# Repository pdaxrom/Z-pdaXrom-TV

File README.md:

# Z-pdaXrom-TV
FPGA board with TV out

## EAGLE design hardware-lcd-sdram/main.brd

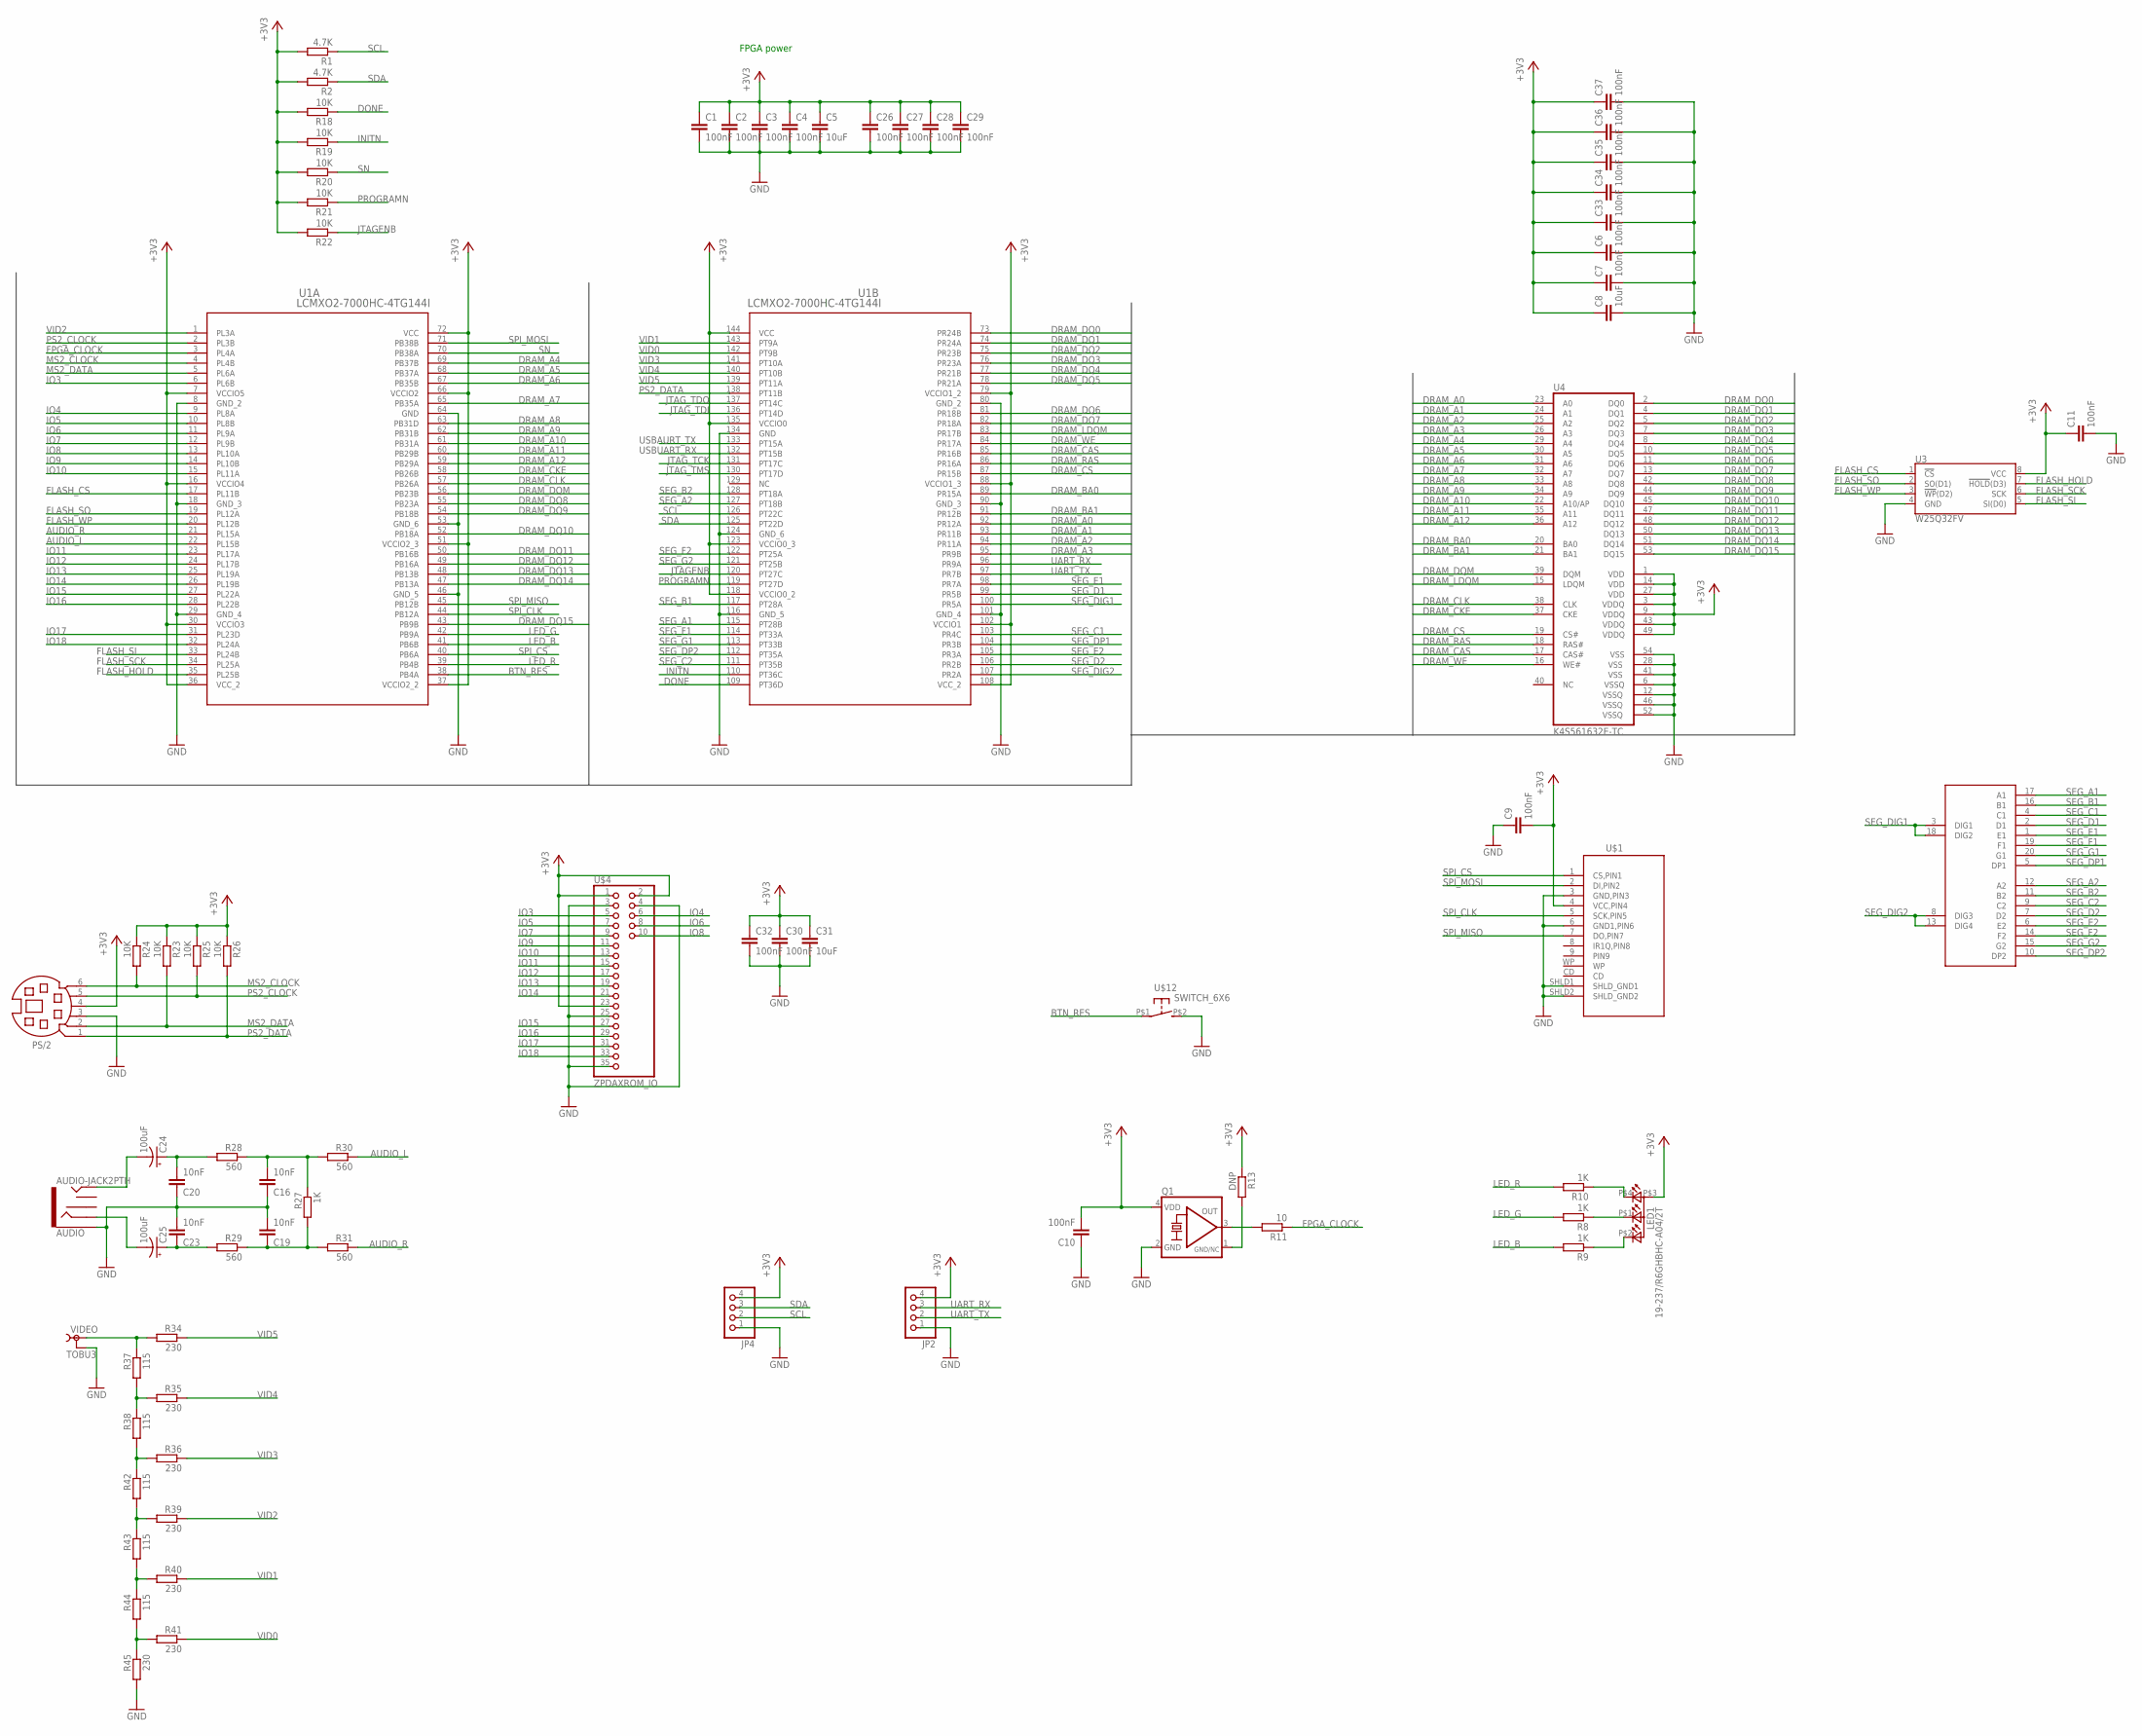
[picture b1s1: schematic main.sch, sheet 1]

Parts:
AUDIO: AUDIO-JACK2PTH; AUDIO-JACK
C1, C2, C3, C4, C6, C7, C9, C10, C11, C26, C27, C28, C29, C30, C32, C33, C34, C35, C36, C37: 100nF; C0603
C5, C8, C31: 10uF; C0805
C16, C19, C20, C23: 10nF; C0603
C24, C25: 100uF; EIA7343
JP2, JP4: PINHD-1X4; 1X04
LED1: 19-237/R6GHBHC-A04/2T
PS/2: MD06SS; MDIN06SS
Q1: KXO-TCXO-CMOS-82; 7.0X5.0_KXO-82-TCXO
R1, R2: 4.7K; R0603
R8, R9, R10, R27: 1K; R0603
R11: 10; R0603
R13: DNP; R0603
R18, R19, R20, R21, R22, R23, R24, R25, R26: 10K; R0603
R28, R29, R30, R31: 560; R0603
R34, R35, R36, R39, R40, R41, R45: 230; R0603
R37, R38, R42, R43, R44: 115; R0603
U1: LCMXO2-7000HC-4TG144I; TQFP144
U3: W25Q32FV; SOIC-8
U4: K4S561632E-TC; TSOP54
U$1: FCI_SD_SOCKET; SD-MMC_SOCKET-PP
U$3: GS2020CR-G; GS2020CR
U$4: ZPDAXROM_IO; 2X18_ZPDAXROM_IO
U$12: SWITCH_6X6
VIDEO: TOBU3

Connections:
+3V3: C1.1, C2.1, C3.1, C4.1, C5.1, C6.1, C7.1, C8.1, C9.2, C10.2, C11.1, C26.1, C27.1, C28.1, C29.1, C30.1, C31.1, C32.1, C33.1, C34.1, C35.1, C36.1, C37.1, JP2.4, JP4.4, LED1.P$3 (A), PS/2.4, Q1.4 (VDD), R1.2, R2.2, R13.1, R18.2, R19.2, R20.2, R21.2, R22.2, R23.1, R24.1, R25.1, R26.1, U1.7 (VCCIO5), U1.16 (VCCIO4), U1.30 (VCCIO3), U1.36 (VCC_2), U1.37 (VCCIO2_2), U1.51 (VCCIO2_3), U1.66 (VCCIO2), U1.72 (VCC), U1.79 (VCCIO1_2), U1.88 (VCCIO1_3), U1.102 (VCCIO1), U1.108 (VCC_2), U1.118 (VCCIO0_2), U1.123 (VCCIO0_3), U1.135 (VCCIO0), U1.144 (VCC), U3.8 (VCC), U4.1 (VDD), U4.3 (VDDQ), U4.9 (VDDQ), U4.14 (VDD), U4.27 (VDD), U4.43 (VDDQ), U4.49 (VDDQ), U$1.4 (VCC,PIN4), U$4.1, U$4.2, U$4.23; also elsewhere on the board
AUDIO_L: R30.1, U1.22 (PL15B)
AUDIO_R: R31.1, U1.21 (PL15A)
BTN_RES: U1.38 (PB4A), U$12.P$1
DONE: R18.1, U1.109 (PT36D)
DRAM_A0: U1.92 (PR12A), U4.23 (A0)
DRAM_A1: U1.93 (PR11B), U4.24 (A1)
DRAM_A2: U1.94 (PR11A), U4.25 (A2)
DRAM_A3: U1.95 (PR9B), U4.26 (A3)
DRAM_A4: U1.69 (PB37B), U4.29 (A4)
DRAM_A5: U1.68 (PB37A), U4.30 (A5)
DRAM_A6: U1.67 (PB35B), U4.31 (A6)
DRAM_A7: U1.65 (PB35A), U4.32 (A7)
DRAM_A8: U1.63 (PB31D), U4.33 (A8)
DRAM_A9: U1.62 (PB31B), U4.34 (A9)
DRAM_A10: U1.61 (PB31A), U4.22 (A10/AP)
DRAM_A11: U1.60 (PB29B), U4.35 (A11)
DRAM_A12: U1.59 (PB29A), U4.36 (A12)
DRAM_BA0: U1.89 (PR15A), U4.20 (BA0)
DRAM_BA1: U1.91 (PR12B), U4.21 (BA1)
DRAM_CAS: U1.85 (PR16B), U4.17 (CAS#)
DRAM_CKE: U1.58 (PB26B), U4.37 (CKE)
DRAM_CLK: U1.57 (PB26A), U4.38 (CLK)
DRAM_CS: U1.87 (PR15B), U4.19 (CS#)
DRAM_DQ0: U1.73 (PR24B), U4.2 (DQ0)
DRAM_DQ1: U1.74 (PR24A), U4.4 (DQ1)
DRAM_DQ2: U1.75 (PR23B), U4.5 (DQ2)
DRAM_DQ3: U1.76 (PR23A), U4.7 (DQ3)
DRAM_DQ4: U1.77 (PR21B), U4.8 (DQ4)
DRAM_DQ5: U1.78 (PR21A), U4.10 (DQ5)
DRAM_DQ6: U1.81 (PR18B), U4.11 (DQ6)
DRAM_DQ7: U1.82 (PR18A), U4.13 (DQ7)
DRAM_DQ8: U1.55 (PB23A), U4.42 (DQ8)
DRAM_DQ9: U1.54 (PB18B), U4.44 (DQ9)
DRAM_DQ10: U1.52 (PB18A), U4.45 (DQ10)
DRAM_DQ11: U1.50 (PB16B), U4.47 (DQ11)
DRAM_DQ12: U1.49 (PB16A), U4.48 (DQ12)
DRAM_DQ13: U1.48 (PB13B), U4.50 (DQ13)
DRAM_DQ14: U1.47 (PB13A), U4.51 (DQ14)
DRAM_DQ15: U1.43 (PB9B), U4.53 (DQ15)
DRAM_DQM: U1.56 (PB23B), U4.39 (DQM)
DRAM_LDQM: U1.83 (PR17B), U4.15 (LDQM)
DRAM_RAS: U1.86 (PR16A), U4.18 (RAS#)
DRAM_WE: U1.84 (PR17A), U4.16 (WE#)
FLASH_CS: U1.17 (PL11B), U3.1 (!CS!)
FLASH_HOLD: U1.35 (PL25B), U3.7 (!HOLD!(D3))
FLASH_SCK: U1.34 (PL25A), U3.6 (SCK)
FLASH_SI: U1.33 (PL24B), U3.5 (SI(D0))
FLASH_SO: U1.19 (PL12A), U3.2 (SO(D1))
FLASH_WP: U1.20 (PL12B), U3.3 (!WP!(D2))
FPGA_CLOCK: R11.1, U1.3 (PL4A)
GND: AUDIO.SLEEVE, C1.2, C2.2, C3.2, C4.2, C5.2, C6.2, C7.2, C8.2, C9.1, C10.1, C11.2, C16.1, C19.2, C20.1, C23.2, C26.2, C27.2, C28.2, C29.2, C30.2, C31.2, C32.2, C33.2, C34.2, C35.2, C36.2, C37.2, JP2.1, JP4.1, PS/2.3, Q1.2 (GND), R45.2, U1.8 (GND_2), U1.18 (GND_3), U1.29 (GND_4), U1.46 (GND_5), U1.53 (GND_6), U1.64 (GND), U1.80 (GND_2), U1.90 (GND_3), U1.101 (GND_4), U1.116 (GND_5), U1.124 (GND_6), U1.134 (GND), U3.4 (GND), U4.6 (VSSQ), U4.12 (VSSQ), U4.28 (VSS), U4.41 (VSS), U4.46 (VSSQ), U4.52 (VSSQ), U4.54 (VSS), U$1.3 (GND,PIN3), U$1.6 (GND1,PIN6), U$1.SHLD1 (SHLD_GND1), U$1.SHLD2 (SHLD_GND2), U$4.3, U$4.4, U$4.25, U$4.35, U$12.P$2 (S), VIDEO.2, VIDEO.2@1 (2), VIDEO.2@2 (2); also elsewhere on the board
INITN: R19.1, U1.110 (PT36C)
IO3: U1.6 (PL6B), U$4.5
IO4: U1.9 (PL8A), U$4.6
IO5: U1.10 (PL8B), U$4.7
IO6: U1.11 (PL9A), U$4.8
IO7: U1.12 (PL9B), U$4.9
IO8: U1.13 (PL10A), U$4.10
IO9: U1.14 (PL10B), U$4.11
IO10: U1.15 (PL11A), U$4.13
IO11: U1.23 (PL17A), U$4.15
IO12: U1.24 (PL17B), U$4.17
IO13: U1.25 (PL19A), U$4.19
IO14: U1.26 (PL19B), U$4.21
IO15: U1.27 (PL22A), U$4.27
IO16: U1.28 (PL22B), U$4.29
IO17: U1.31 (PL23D), U$4.31
IO18: U1.32 (PL24A), U$4.33
JTAGENB: R22.1, U1.120 (PT27C)
JTAG_TCK: U1.131 (PT17C); also elsewhere on the board
JTAG_TDI: U1.136 (PT14D); also elsewhere on the board
JTAG_TDO: U1.137 (PT14C); also elsewhere on the board
JTAG_TMS: U1.130 (PT17D); also elsewhere on the board
LED_B: R9.2, U1.41 (PB6B)
LED_G: R8.2, U1.42 (PB9A)
LED_R: R10.2, U1.39 (PB4B)
MS2_CLOCK: PS/2.6, R24.2, U1.4 (PL4B)
MS2_DATA: PS/2.2, R23.2, U1.5 (PL6A)
unnamed: LED1.P$4 (CRED), R10.1
unnamed: Q1.3 (OUT), R11.2
unnamed: LED1.P$1 (CBLUE), R8.1
unnamed: LED1.P$2 (CGREEN), R9.1
unnamed: Q1.1 (GND/NC), R13.2
unnamed: C19.1, R27.2, R29.1, R31.2
unnamed: C16.2, R27.1, R28.1, R30.2
unnamed: AUDIO.TIP, C24.C (-)
unnamed: C23.1, C25.A (+), R29.2
unnamed: C20.2, C24.A (+), R28.2
unnamed: AUDIO.RING, C25.C (-)
unnamed: R34.2, R37.1, VIDEO.1
unnamed: R35.2, R37.2, R38.1
unnamed: R36.2, R38.2, R42.1
unnamed: R39.2, R42.2, R43.1
unnamed: R40.2, R43.2, R44.1
unnamed: R41.2, R44.2, R45.1
PROGRAMN: R21.1, U1.119 (PT27D)
PS2_CLOCK: PS/2.5, R25.2, U1.2 (PL3B)
PS2_DATA: PS/2.1, R26.2, U1.138 (PT11B)
SCL: JP4.2, R1.1, U1.126 (PT22C)
SDA: JP4.3, R2.1, U1.125 (PT22D)
SEG_A1: U1.115 (PT28B), U$3.17 (A1)
SEG_A2: U1.127 (PT18B), U$3.12 (A2)
SEG_B1: U1.117 (PT28A), U$3.16 (B1)
SEG_B2: U1.128 (PT18A), U$3.11 (B2)
SEG_C1: U1.103 (PR4C), U$3.4 (C1)
SEG_C2: U1.111 (PT35B), U$3.9 (C2)
SEG_D1: U1.99 (PR5B), U$3.2 (D1)
SEG_D2: U1.106 (PR2B), U$3.7 (D2)
SEG_DIG1: U1.100 (PR5A), U$3.3 (DIG1), U$3.18 (DIG2)
SEG_DIG2: U1.107 (PR2A), U$3.8 (DIG3), U$3.13 (DIG4)
SEG_DP1: U1.104 (PR3B), U$3.5 (DP1)
SEG_DP2: U1.112 (PT35A), U$3.10 (DP2)
SEG_E1: U1.98 (PR7A), U$3.1 (E1)
SEG_E2: U1.105 (PR3A), U$3.6 (E2)
SEG_F1: U1.114 (PT33A), U$3.19 (F1)
SEG_F2: U1.122 (PT25A), U$3.14 (F2)
SEG_G1: U1.113 (PT33B), U$3.20 (G1)
SEG_G2: U1.121 (PT25B), U$3.15 (G2)
SN: R20.1, U1.70 (PB38A)
SPI_CLK: U1.44 (PB12A), U$1.5 (SCK,PIN5)
SPI_CS: U1.40 (PB6A), U$1.1 (CS,PIN1)
SPI_MISO: U1.45 (PB12B), U$1.7 (DO,PIN7)
SPI_MOSI: U1.71 (PB38B), U$1.2 (DI,PIN2)
UART_RX: JP2.3, U1.96 (PR9A)
UART_TX: JP2.2, U1.97 (PR7B)
USBAURT_TX: U1.133 (PT15A); also elsewhere on the board
USBUART_RX: U1.132 (PT15B); also elsewhere on the board
VID0: R41.1, U1.142 (PT9B)
VID1: R40.1, U1.143 (PT9A)
VID2: R39.1, U1.1 (PL3A)
VID3: R36.1, U1.141 (PT10A)
VID4: R35.1, U1.140 (PT10B)
VID5: R34.1, U1.139 (PT11A)

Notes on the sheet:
FPGA power

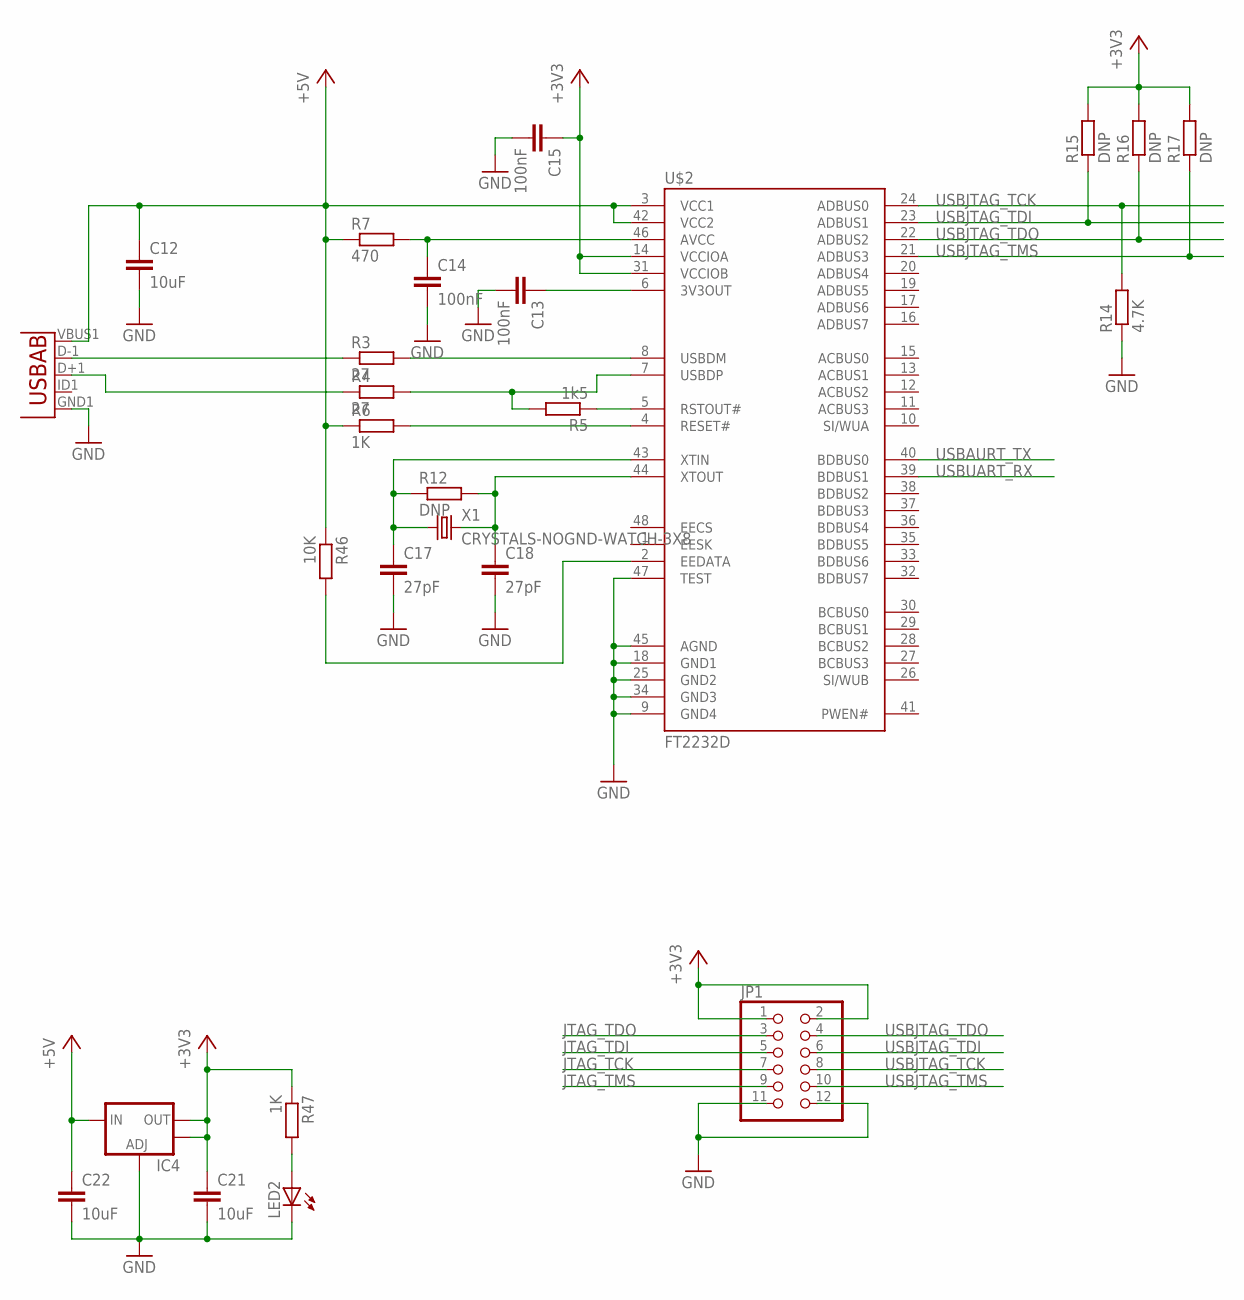
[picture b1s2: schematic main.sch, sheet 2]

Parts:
C12, C21, C22: 10uF; C0805
C13, C14, C15: 100nF; C0603
C17, C18: 27pF; C0603
IC4: V_REG_LM1117SOT223; SOT223
JP1: PINHD-2X6; 2X06
LED2: LEDCHIPLED_0603; CHIPLED_0603
R3, R4: 27; R0603
R5: 1k5; R0603
R6, R47: 1K; R0603
R7: 470; R0603
R12, R15, R16, R17: DNP; R0603
R14: 4.7K; R0603
R46: 10K; R0603
U2: USB""; USB-MICRO-SMD
U$2: FT2232D; LQFP-48
X1: CRYSTALS-NOGND-WATCH-3X8; WATCH-3X8

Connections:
+3V3: C15.1, C21.1, IC4.2 (OUT), IC4.4 (OUT), JP1.1, JP1.2, R15.2, R16.2, R17.2, R47.1, U$2.14 (VCCIOA), U$2.31 (VCCIOB); also elsewhere on the board
+5V: C12.1, C22.1, IC4.3 (IN), R6.1, R7.1, R46.1, U2.VBUS1 (VBUS), U$2.3 (VCC1), U$2.42 (VCC2)
GND: C12.2, C13.2, C14.2, C15.2, C17.2, C18.2, C21.2, C22.2, IC4.1 (ADJ), JP1.11, JP1.12, LED2.C, R14.1, U2.GND1 (GND), U$2.9 (GND4), U$2.18 (GND1), U$2.25 (GND2), U$2.34 (GND3), U$2.45 (AGND), U$2.47 (TEST); also elsewhere on the board
JTAG_TCK: JP1.7; also elsewhere on the board
JTAG_TDI: JP1.5; also elsewhere on the board
JTAG_TDO: JP1.3; also elsewhere on the board
JTAG_TMS: JP1.9; also elsewhere on the board
unnamed: R3.1, U2.D-1 (D-)
unnamed: R4.1, U2.D+1 (D+)
unnamed: R3.2, U$2.8 (USBDM)
unnamed: C13.1, U$2.6 (3V3OUT)
unnamed: C14.1, R7.2, U$2.46 (AVCC)
unnamed: R4.2, R5.2, U$2.7 (USBDP)
unnamed: R5.1, U$2.5 (RSTOUT#)
unnamed: R6.2, U$2.4 (RESET#)
unnamed: C17.1, R12.1, U$2.43 (XTIN), X1.1
unnamed: C18.1, R12.2, U$2.44 (XTOUT), X1.2
unnamed: R46.2, U$2.2 (EEDATA)
unnamed: LED2.A, R47.2
USBAURT_TX: U$2.40 (BDBUS0); also elsewhere on the board
USBJTAG_TCK: JP1.8, R14.2, U$2.24 (ADBUS0)
USBJTAG_TDI: JP1.6, R15.1, U$2.23 (ADBUS1)
USBJTAG_TDO: JP1.4, R16.1, U$2.22 (ADBUS2)
USBJTAG_TMS: JP1.10, R17.1, U$2.21 (ADBUS3)
USBUART_RX: U$2.39 (BDBUS1); also elsewhere on the board

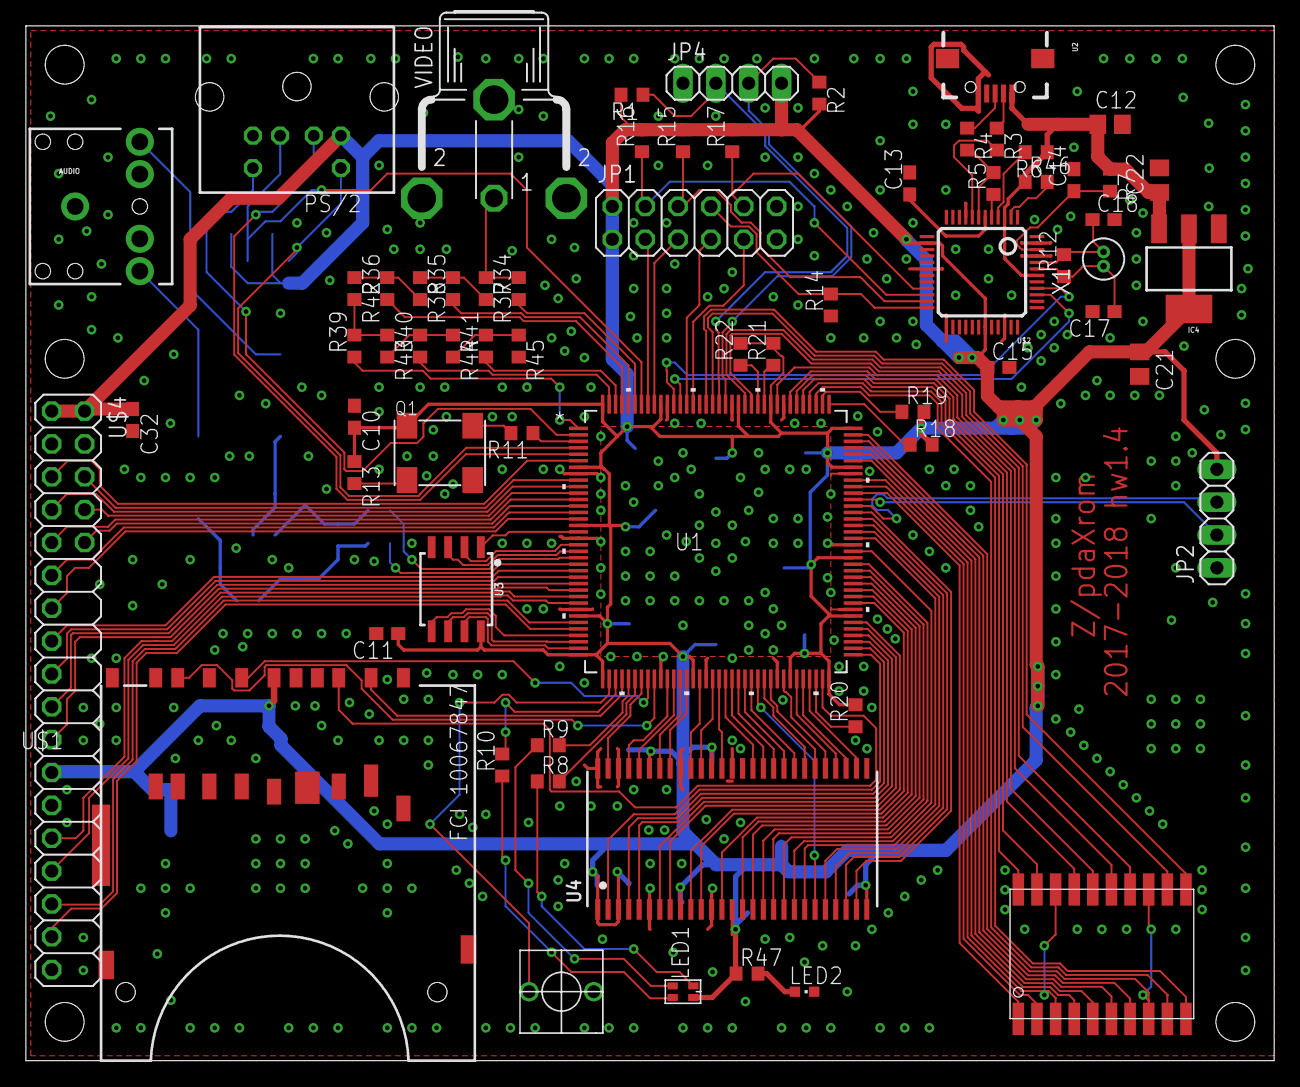
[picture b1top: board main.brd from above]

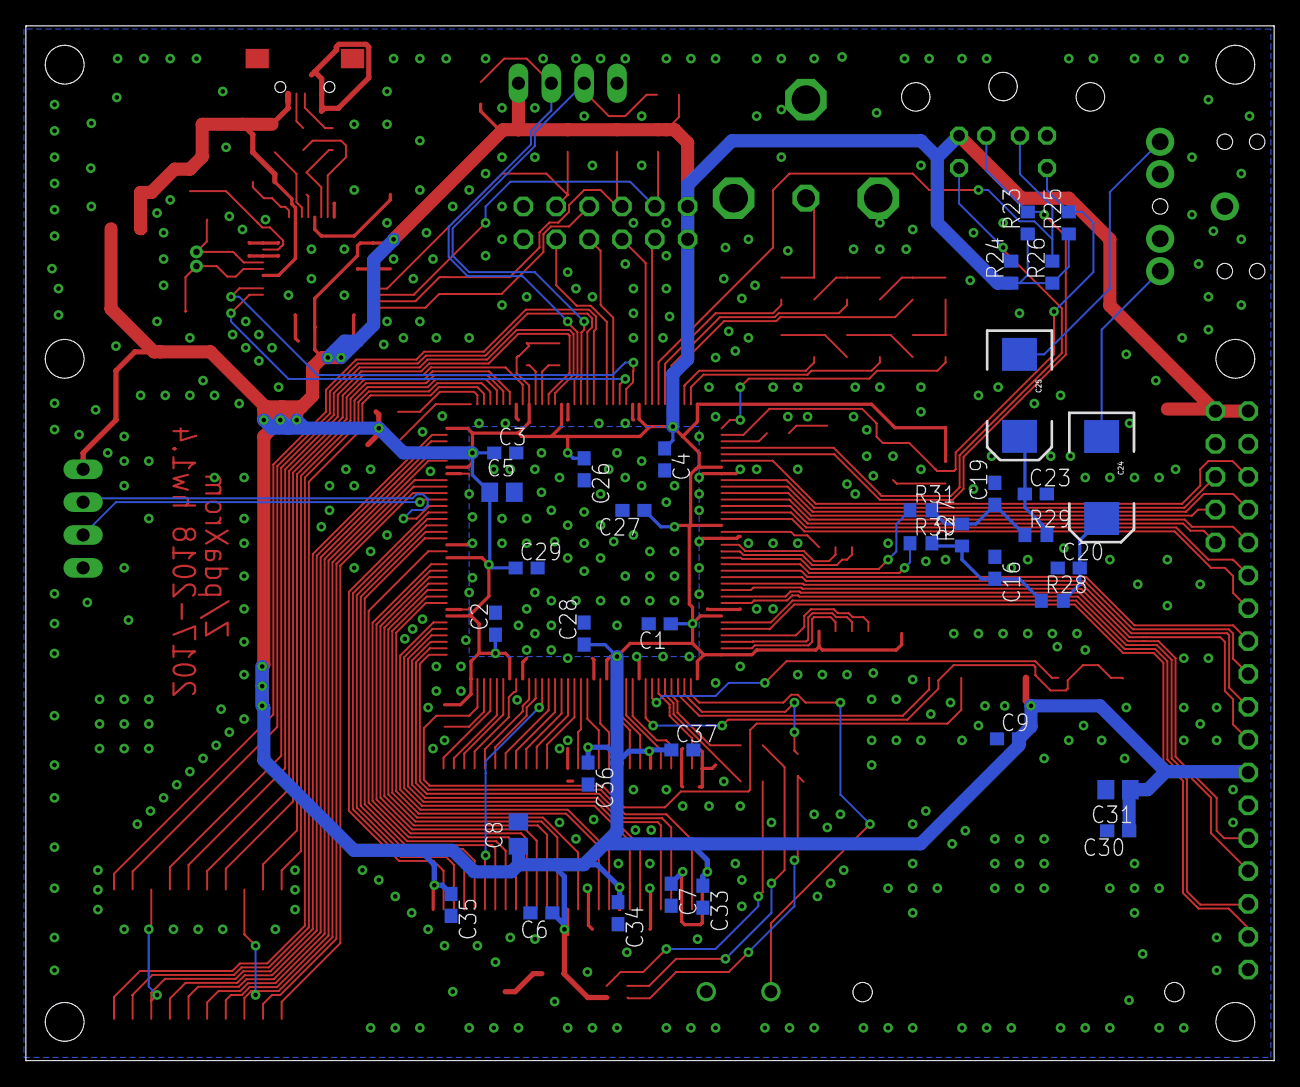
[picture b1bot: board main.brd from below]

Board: 2 copper layers, 96.5 x 80.0 mm, 102 parts (35 on the bottom side), 151 nets.

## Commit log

2018-04-19 initial hw 1.3
2018-04-19 6MHz TSX3225 replaced with 6x3
2018-04-24 schematic fixes
2018-04-24 first project - rgb leds, hex counter and reset
2018-04-24 programmer settings
2018-04-24 6-bit video dac
2018-04-24 pal color demo (papilio tv output wing)
2018-04-24 p601zero-plus computer initial
2018-04-24 fixed new board
2018-04-24 Schematic and pcb fixes. Removed vid6 from video dac, io0 from GPIO port. Missed keyboard lines connected: ps2data to vid6, ps2clk to io0
2018-04-26 3.5 inch spi lcd port added
2018-04-27 ft2232d jtag channel detach utility
2018-04-27 removed wrong release function
2018-04-27 static ram support initial
2018-04-27 fixed vpu logic, bus ready signal added
2018-04-27 project update
2018-05-11 SRAM replaced with SDRAM
2018-05-11 Fixed for WSL env
2018-05-11 ignore zero vectors
2018-05-11 Updated for hw1.3
2018-05-11 sd card r/w driver test
2018-05-11 fix read
2018-05-11 enabled boot from sd
2018-05-11 booting from FAT16 partition (offset 2048)
2018-05-12 fix build
2018-05-12 BUFFALO
2018-05-16 idiv fix initial
2018-05-16 fixed remainder
2018-06-22 fixed idiv and mul

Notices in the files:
parts and their libraries:
SparkFun-IC-Memory: Licensing: Creative Commons ShareAlike 4.0 International - https://creativecommons.org/licenses/by-sa/4.0
crystal-geyer_V1_0: Copyright: Geyer-Electronic
